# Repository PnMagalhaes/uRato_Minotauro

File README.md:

# uRato_Minotauro
Maze runner competition

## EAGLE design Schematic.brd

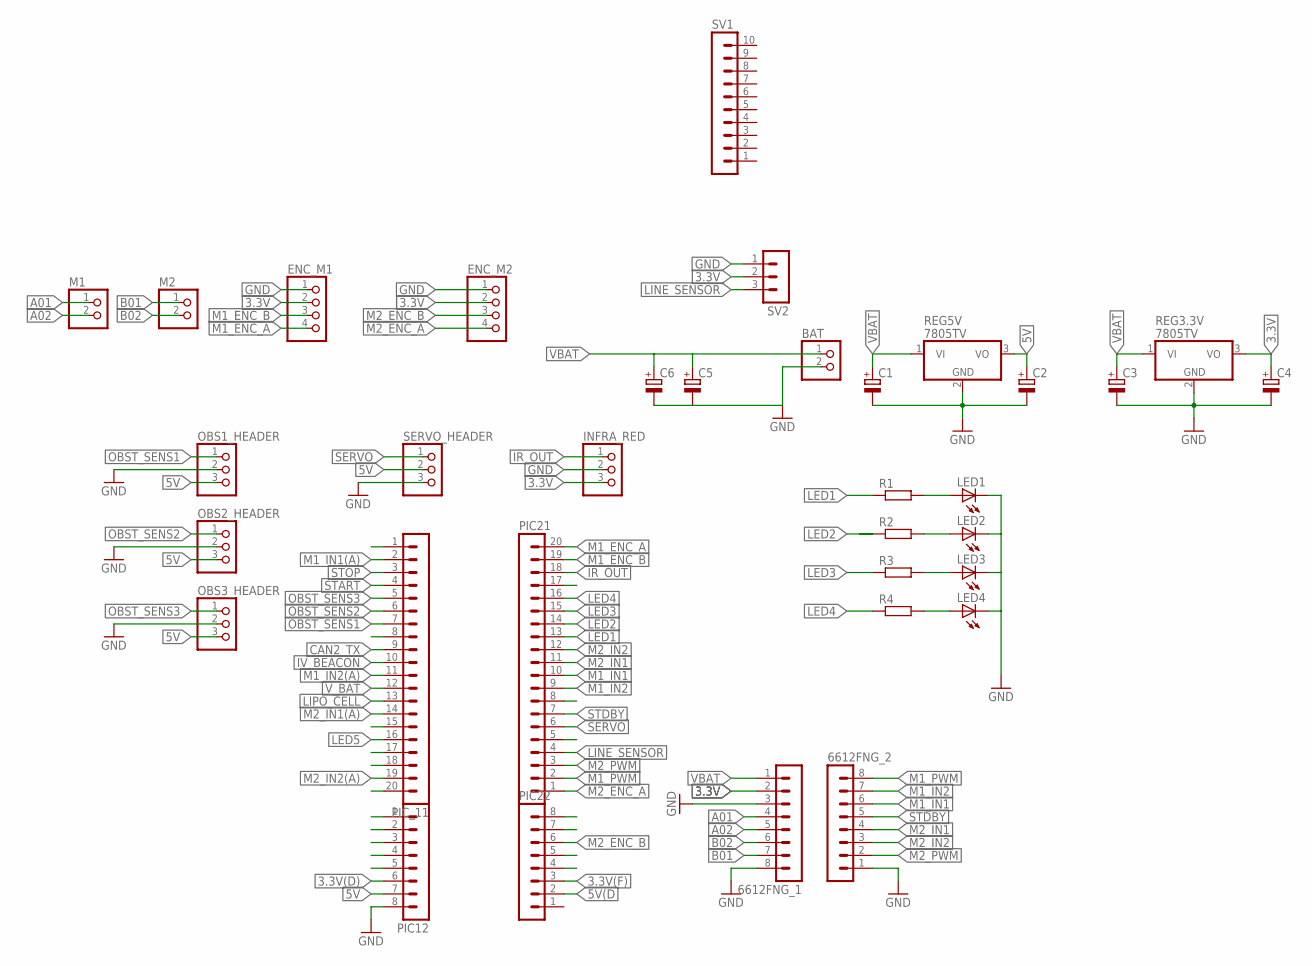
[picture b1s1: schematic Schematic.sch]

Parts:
6612FNG_1, 6612FNG_2: MA08-1
BAT: PINHD-1X2; 1X02
C1, C2, C3, C4, C5, C6: CPOL-EUE2,5-6E; E2,5-6E
ENC_M1, ENC_M2: PINHD-1X4; 1X04
INFRA_RED: PINHD-1X3; 1X03
LED1, LED2, LED3, LED4: LED3MM
M1, M2: PINHD-1X2; 1X02
OBS1_HEADER, OBS2_HEADER, OBS3_HEADER: PINHD-1X3; 1X03
PIC12, PIC22: MA08-1
PIC21: MA20-1
PIC_11: MA20-1
R1, R2, R3, R4: R-EU_0207/7; 0207/7
REG3.3V, REG5V: 7805TV; TO220V
SERVO_HEADER: PINHD-1X3; 1X03
SV1: MA10-1
SV2: MA03-1

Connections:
3.3V: 6612FNG_1.2, C4.+, ENC_M1.2, ENC_M2.2, INFRA_RED.3, REG3.3V.3 (VO), SV2.2
3.3V(D): PIC12.6
3.3V(F): PIC22.3
5V: C2.+, OBS1_HEADER.3, OBS2_HEADER.3, OBS3_HEADER.3, PIC12.7, REG5V.3 (VO), SERVO_HEADER.2
5V(D: PIC22.2
A01: 6612FNG_1.4, M1.1
A02: 6612FNG_1.5, M1.2
B01: 6612FNG_1.7, M2.1
B02: 6612FNG_1.6, M2.2
CAN1_RX: PIC_11.17
CAN1_TX: PIC_11.18
CAN2_RX: PIC_11.15
CAN2_TX: PIC_11.9
DIR_485: PIC21.17
GND: 6612FNG_1.3, 6612FNG_1.8, 6612FNG_2.1, BAT.2, C1.-, C2.-, C3.-, C4.-, C5.-, C6.-, ENC_M1.1, ENC_M2.1, INFRA_RED.2, LED1.K (C), LED2.K (C), LED3.K (C), LED4.K (C), OBS1_HEADER.2, OBS2_HEADER.2, OBS3_HEADER.2, PIC12.8, REG3.3V.2 (GND), REG5V.2 (GND), SERVO_HEADER.3, SV2.1
I2C_SCL: PIC22.8
I2C_SDA: PIC22.7
IO2_U1TX: PIC21.5
IO4: PIC21.8
IR_OUT: INFRA_RED.1, PIC21.18
IV_BEACON: PIC_11.10
LED1: PIC21.13, R1.1
LED2: PIC21.14, R2.1
LED3: PIC21.15, R3.1
LED4: PIC21.16, R4.1
LED5: PIC_11.16
LINE_SENSOR: PIC21.4, SV2.3
LIPO_CELL: PIC_11.13
M1_ENC_A: ENC_M1.4, PIC21.20
M1_ENC_B: ENC_M1.3, PIC21.19
M1_IN1: 6612FNG_2.6, PIC21.10
M1_IN1(A): PIC_11.2
M1_IN2: 6612FNG_2.7, PIC21.9
M1_IN2(A): PIC_11.11
M1_PWM: 6612FNG_2.8, PIC21.2
M2_ENC_A: ENC_M2.4, PIC21.1
M2_ENC_B: ENC_M2.3, PIC22.6
M2_IN1: 6612FNG_2.4, PIC21.11
M2_IN1(A): PIC_11.14
M2_IN2: 6612FNG_2.3, PIC21.12
M2_IN2(A): PIC_11.19
M2_PWM: 6612FNG_2.2, PIC21.3
unnamed: LED1.A, R1.2
unnamed: LED2.A, R2.2
unnamed: LED3.A, R3.2
unnamed: LED4.A, R4.2
OBST_SENS1: OBS1_HEADER.1, PIC_11.7
OBST_SENS2: OBS2_HEADER.1, PIC_11.6
OBST_SENS3: OBS3_HEADER.1, PIC_11.5
PGC: PIC_11.1
PGD: PIC_11.8
SERVO: PIC21.6, SERVO_HEADER.1
START: PIC_11.4
STDBY: 6612FNG_2.5, PIC21.7
STOP: PIC_11.3
U2_RC: PIC_11.20
U2_TX: PIC12.1
U6_TX: PIC22.4
VBAT: 6612FNG_1.1, BAT.1, C1.+, C3.+, C5.+, C6.+, REG3.3V.1 (VI), REG5V.1 (VI)
V_BAT: PIC_11.12

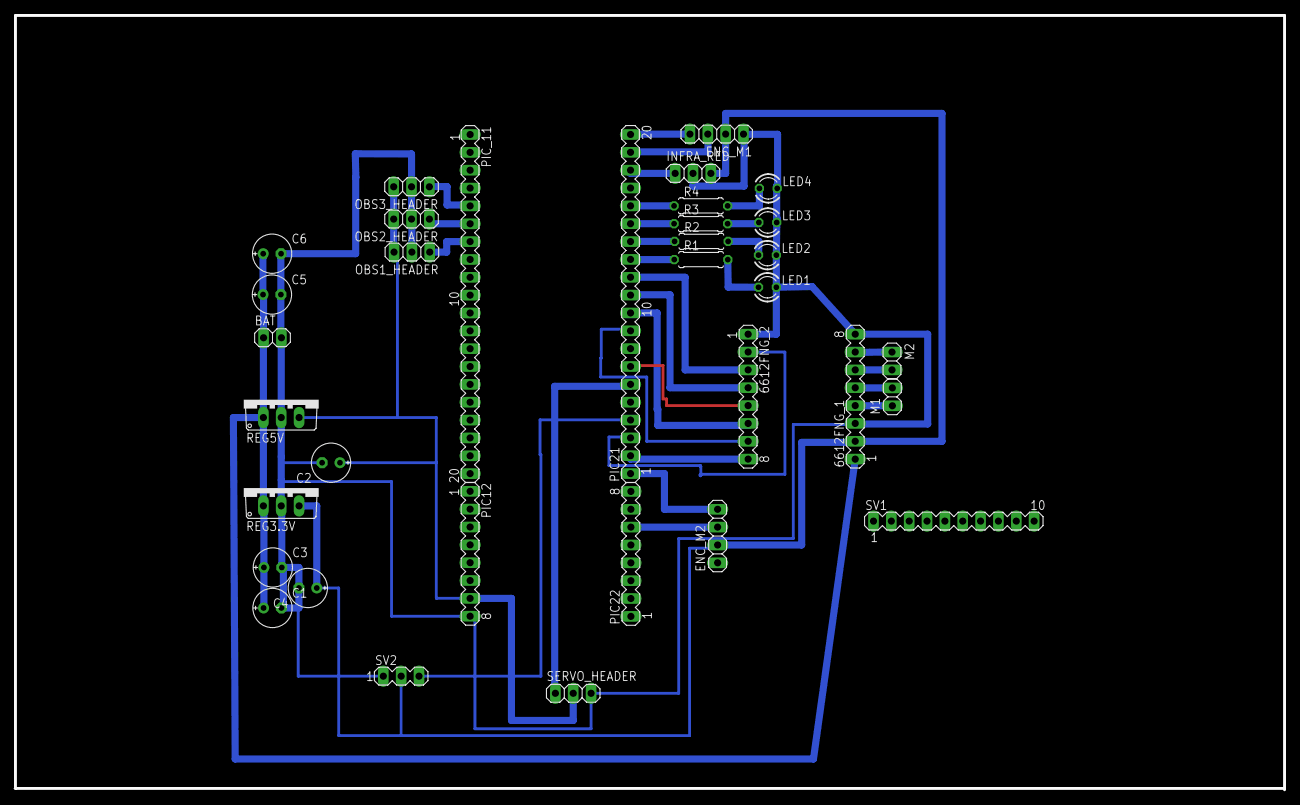
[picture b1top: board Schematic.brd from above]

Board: 2 copper layers, 180.6 x 110.2 mm, 34 parts (0 on the bottom side), 33 nets.

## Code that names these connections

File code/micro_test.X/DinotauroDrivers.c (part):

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
// ****************************************************************************
//
#define M1_IN1 LATBbits.LATB5
#define M1_IN2 LATBbits.LATB6
#define M2_IN1 LATBbits.LATB14
#define M2_IN2 LATBbits.LATB8
#define STDBY  LATBbits.LATB7

#define LED1   LATEbits.LATE0
#define LED2   LATEbits.LATE1
#define LED3   LATEbits.LATE2
#define LED4   LATEbits.LATE3

#define LINE_SENSOR  LATDbits.LATD2

#define M1_FORWARD M1_IN1=0; M1_IN2=1
#define M1_REVERSE M1_IN1=1; M1_IN2=0

#define M2_FORWARD M2_IN1=0; M2_IN2=1
#define M2_REVERSE M2_IN1=1; M2_IN2=0

// ****************************************************************************
// Servo constants	(do not change any of these values)
//
#define POS_LEFT		-15
#define POS_RIGHT		15
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// IO Config
//
//  1-Bridge control
	STDBY = 1;				// Half-Bridge ON

    TRISBbits.TRISB5 = OUT;
    TRISBbits.TRISB6 = OUT;
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    TRISBbits.TRISB8 = OUT;
    TRISBbits.TRISB14 = OUT;
    
	M1_IN1 = M1_IN2 = 0;	// STOP
	M2_IN1 = M2_IN2 = 0;	// STOP

	LATDbits.LATD5 = OUT;		// STDBY
    LATGbits.LATG9 = OUT;  		// M1_IN1
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
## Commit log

2018-05-07 Chaves DevDrivers added
2018-05-08 Revisão dos pinouts- Beacon, sharp 1 e 3, line sensor a funcionar
2018-05-08 Eagle files
2018-05-08 fuuuck
2018-05-11 New cad files
2018-06-21 pictures
